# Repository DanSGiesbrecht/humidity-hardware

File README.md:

# Wireless Humidity Sensor

---

---

---

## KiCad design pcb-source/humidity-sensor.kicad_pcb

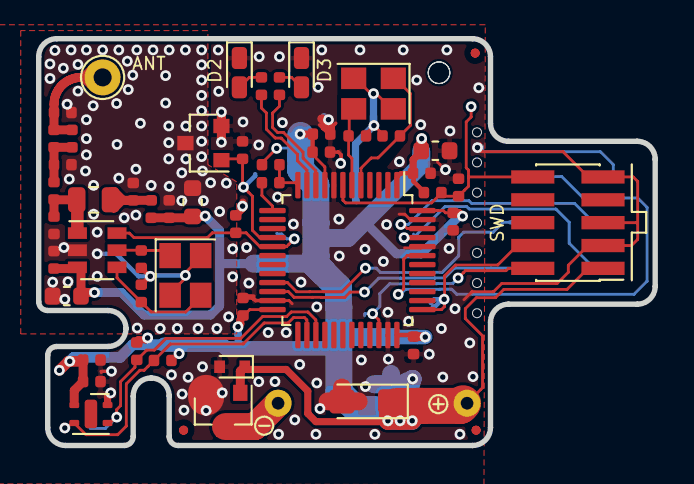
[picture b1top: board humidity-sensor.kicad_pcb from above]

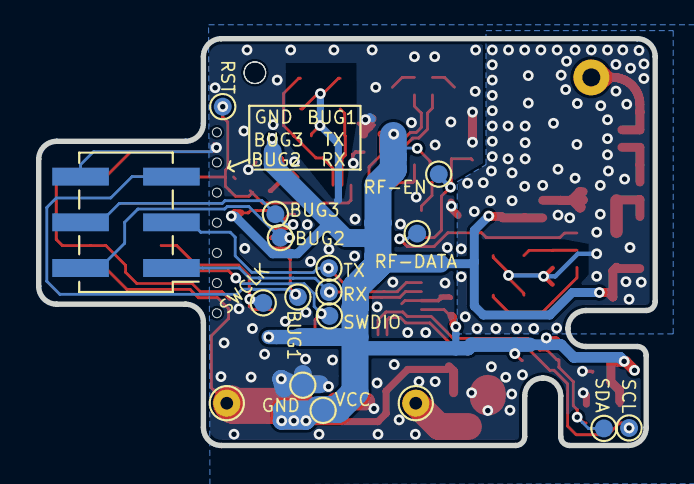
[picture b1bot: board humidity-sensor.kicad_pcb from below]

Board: 2 copper layers, 34.3 x 22.6 mm, 72 parts (17 on the bottom side), 30 nets.

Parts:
AE1: Antenna; TestPoint_THTPad_D2.0mm_Drill1.0mm
C1, C2: 10pF C0G; C_0402_1005Metric
C3: 22uF 10V; CP_EIA-3216-18_Kemet-A
C4, C8, C10, C11, C12, C14, C18, C25: 0.1uF; C_0402_1005Metric
C5, C6, C17, C19, C21, C22: DNU; C_0402_1005Metric
C7, C13, C24: 10uF; C_0603_1608Metric
C9, C16: 1uF; C_0402_1005Metric
C15: 100pF C0G; C_0402_1005Metric
C20: 12pF C0G; C_0402_1005Metric
C23: 4.7pF C0G; C_0402_1005Metric
D1: TVS; D_SOD-523
D2, D3: LED; LED_0603_1608Metric_Castellated
FID1, FID1#2, FID2, FID2#2, FID3, FID3#2: Fiducial; Fiducial_0.5mm_Mask1mm
H1, H2: MountingHole_Pad; TestPoint_THTPad_D1.5mm_Drill0.7mm
J1: Conn_ARM_JTAG_SWD_10; PinHeader_2x05_P1.27mm_Vertical_SMD
J2: Conn_02x03_Odd_Even; PinHeader_2x03_P2.54mm_Vertical_SMD
L1: 820nH; L_0805_2012Metric
L2: 68nH; L_0402_1005Metric
Q1, Q2: Q_NMOS_GSD; SOT-23
R1, R3: 300R; R_0402_1005Metric
R2: 1M; R_0402_1005Metric
R4, R6, R9, R10: 100K; R_0402_1005Metric
R5: 0R; R_0402_1005Metric
R7, R8: 10K; R_0402_1005Metric
TP1: TP_RF_EN; TestPoint_Pad_D1.0mm
TP2: TP_RF_DATA; TestPoint_Pad_D1.0mm
TP3: TP_HUM_SDA; TestPoint_Pad_D1.0mm
TP4: TP_HUM_SCL; TestPoint_Pad_D1.0mm
TP5: TP_UART_TX; TestPoint_Pad_D1.0mm
TP6: TP_UART_RX; TestPoint_Pad_D1.0mm
TP7: TP_DEBUG_1; TestPoint_Pad_D1.0mm
TP8: TP_DEBUG_2; TestPoint_Pad_D1.0mm
TP9: TP_DEBUG_3; TestPoint_Pad_D1.0mm
TP10: TP_SWDIO; TestPoint_Pad_D1.0mm
TP11: TP_SWDCLK; TestPoint_Pad_D1.0mm
TP12: TP_nRST; TestPoint_Pad_D1.0mm
TP13: TP_VCC; TestPoint_Pad_D1.0mm
TP14: TP_GND; TestPoint_Pad_D1.0mm
U1: STM32L051C8Tx; LQFP-48_7x7mm_P0.5mm
U2: SHTC3; Sensirion_DFN-4-1EP_2x2mm_P1mm_EP0.7x1.6mm
U3: SYN115; SOT-23-6
Y1: 13.56MHz; Crystal_SMD_3225-4Pin_3.2x2.5mm
Y2: DNU; Crystal_SMD_3225-4Pin_3.2x2.5mm

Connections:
/DEBUG_1: J2.5, TP7.1, U1.43
/DEBUG_2: J2.2, TP8.1, U1.45
/DEBUG_3: J2.4, TP9.1, U1.46
/HUM_SCL: R8.2, TP4.1, U1.26, U2.2
/HUM_SDA: R7.2, TP3.1, U1.27, U2.3
/RF_DATA: R4.1, TP2.1, U1.17, U3.6
/RF_EN: Q2.1, R2.1, TP1.1, U1.16
/SWCLK: J1.4, TP11.1, U1.37
/SWDIO: J1.2, TP10.1, U1.34
/UART_RX: J2.1, TP6.1, U1.22
/UART_TX: J2.3, TP5.1, U1.21
GND: C3.2, C4.2, C5.2, C6.1, C7.2, C8.2, C9.2, C10.2, C11.2, C12.2, C16.2, C18.2, C25.2, D1.2, D2.1, D3.1, J1.3, J1.5, J1.9, J2.6, Q1.2, Q2.2, R2.2, R4.2, TP14.1, U1.8, U1.23, U1.35, U1.44, U1.47, U2.4, Y2.2, Y2.4
GNDA: C1.2, C2.1, C13.2, C14.2, C15.2, C17.2, C19.1, C21.1, C23.1, C24.2, Q2.3, U3.2, Y1.2, Y1.4
unnamed: AE1.1, C22.2, C23.2, L2.1
unnamed: C1.1, U3.5, Y1.1
unnamed: C2.2, U3.4, Y1.3
unnamed: C5.1, U1.5, Y2.1
unnamed: C6.2, U1.6, Y2.3
unnamed: C17.1, L1.1, R5.2
unnamed: C19.2, C20.2, L1.2, U3.1
unnamed: C20.1, C21.2, C22.1, L2.2
unnamed: C25.1, J1.10, R6.2, TP12.1, U1.7
unnamed: D2.2, R1.2
unnamed: D3.2, R3.2
unnamed: H1.1, Q1.3
unnamed: R1.1, U1.11
unnamed: R3.1, U1.10
unnamed: R9.2, R10.1, U1.12
unnamed: R10.2, U1.13
VCC: C3.1, C4.1, C7.1, C8.1, C9.1, C10.1, C11.1, C12.1, C13.1, C14.1, C15.1, C16.1, C18.1, C24.1, D1.1, H2.1, J1.1, Q1.1, R5.1, R6.1, R7.1, R8.1, R9.1, TP13.1, U1.1, U1.9, U1.24, U1.36, U1.48, U2.1, U3.3

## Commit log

2019-11-09 Add kicad libraries as submodules
    Add kicad-footprints
    Add kicad-symbols
    Add kicad-packages3D
2019-11-09 Exclude local lib-tables
2019-11-09 Add script for library setup
2019-11-09 Copy over lib-tables
2019-11-10 Fix lib-table locations
    - Update sym/fp-lib-table paths in script
    - Add to .gitignore
2019-11-10 Add autosave file to gitignore
2019-11-10 Add SYN115 to symbol lib
2019-11-10 Add SYN115 to schematic
2019-11-12 Work on schematic and layout
2019-11-13 Work on schem and layout
2019-11-15 Work on schem and PCB
2019-11-17 Work on layout
2019-11-19 Finish routing
2019-11-20 Reduce DRC, add silk
2019-11-24 Add curved RF trace, update rev template
2019-11-24 Update template
2019-11-24 Add 1.2mm NPTH
2019-11-24 Add 1.2mm NPTH for alignment
2019-11-27 Modify fiducials
    Library footprint doesn't create copper pull-back from
    soldermask opening.
2019-12-08 Update revision, beef trace, clean GND
    - Change from rev '0.1.0' to 'r0.1'.
    - Beef up GND trace for humidity sensor.
    - Tidy GND pours/traces.
2019-12-08 Add kicadScripts as submodule
2019-12-08 Set aux origin
2019-12-09 Generate modified footprint library
    - Altered 3D filepath
    - Add generated directory to .gitignore
2019-12-10 Update XTAL GND
2019-12-10 Revert OSHW logo to soldermask layer
2019-12-10 Add name to title blocks
2019-12-10 Hide "TP" on Bottom Fab layer
2019-12-10 Repour GND
2019-12-10 Update submodule - gerbers for OSHpark
2019-12-10 Add 3D KiCad renders
2019-12-12 Add 2D renders of r0.1
2020-01-11 Convert submodule URLs to HTTPS
    Previously, if a user decided to clone the repository and didn't
    have SSH set up with GitHub, the submodules wouldn't update.
2020-01-12 Add OS-path logic
    - Identify Cygwin, Mingw, Darwin (Mac OS), Linux.
    - If needed, convert sym/fp-lib-table, 3D model paths to
    Windows-friendly paths ( /c/ -> c:/ ).
2020-01-12 Remove Windows-OS prompt
    It's unnecessary to ask the user to confirm that they're using
    Windows OS.
2020-01-13 Spawn multiple processes (one per file)
